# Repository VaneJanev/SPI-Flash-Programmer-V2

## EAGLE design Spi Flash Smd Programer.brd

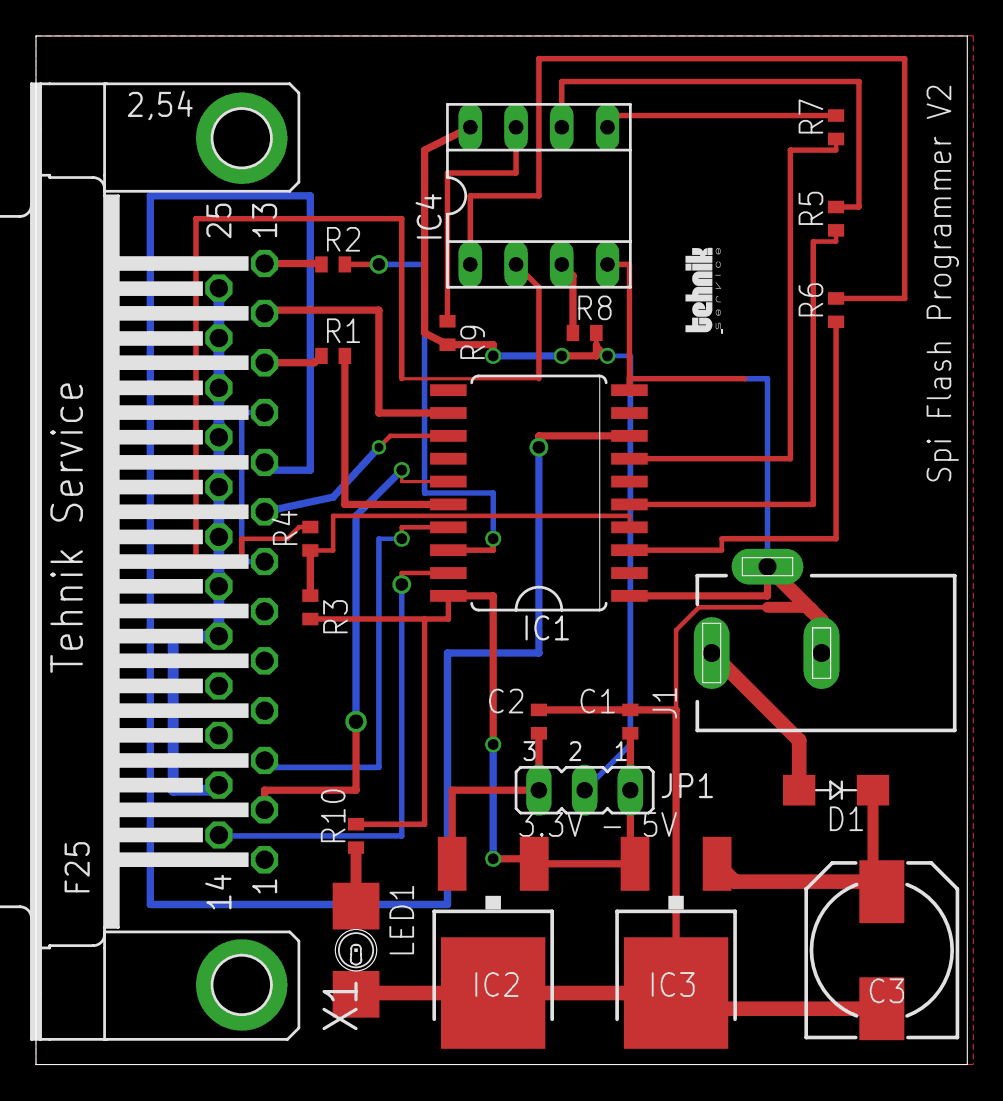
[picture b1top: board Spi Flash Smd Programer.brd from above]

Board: 2 copper layers, 51.7 x 57.1 mm, 23 parts (0 on the bottom side), 29 nets.

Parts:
C1, C2: C0402
C3: 150CLZ-0810
D1: GF1; SMA-DO214AC
E$1: LOGOT
IC1: 74LS244; SO20W
IC2: LM1117; DPACK
IC3: 7805; DPACK
IC4: SPI; SOCKET-08
J1: DCJ0202
JP1: JP2
LED1: P47F-TOP
R1, R2, R3, R4, R5, R6, R7, R8, R9, R10: R1005
X1: F25HP

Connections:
GND: C1.2, C2.2, C3.-, IC1.1, IC1.10, IC2.4, IC3.4, IC4.4, J1.2, J1.3, LED1.C
unnamed: C2.1, IC2.3, JP1.3
unnamed: C3.+, D1.K, IC3.1
unnamed: R1.1, X1.11
unnamed: IC1.4, R3.1, R4.1
unnamed: IC1.5, R5.1
unnamed: IC1.3, R6.1
unnamed: IC1.7, R7.1
unnamed: IC4.3, R8.1
unnamed: IC4.7, R9.1
unnamed: IC4.8, JP1.2, R8.2, R9.2
unnamed: IC4.2, R4.2
unnamed: IC4.1, R6.2
unnamed: IC4.5, R7.2
unnamed: IC4.6, R5.2
unnamed: R2.1, X1.13
unnamed: IC1.15, X1.2
unnamed: IC1.17, X1.3
unnamed: X1.7, X1.10
unnamed: IC1.12, X1.12
unnamed: IC1.19, X1.14
unnamed: X1.15, X1.18, X1.19, X1.20, X1.21, X1.22, X1.23, X1.24, X1.25
unnamed: IC1.13, X1.8
unnamed: IC1.8, X1.9
unnamed: IC1.16, R1.2
unnamed: IC1.18, R2.2
unnamed: D1.A, J1.1
unnamed: LED1.A, R10.1
VCC: C1.1, IC1.20, IC2.1, IC3.3, JP1.1, R3.2, R10.2

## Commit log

2015-06-03 :confetti_ball: Added .gitattributes
2015-06-03 SPI Flash Programmer V2
